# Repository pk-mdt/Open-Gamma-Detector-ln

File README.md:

# Open Gamma Detector

**This is a revised hardware design from the original 3.0 version of the project. The project has been redesigned in Kicad and incorporates an impedance controlled 4 layer board design, as well as micro SMA connectors to the SiPM**

These changed from the original project are hardware only, the original software works and has been fully tested on these revisions. Here is an assembled prototype with a Sodium Iodide Crystal from OST Photonics.

Revised custom layout and hardware for a hackable scintillation counter and multichannel analyzer (MCA) all-in-one device using a popular NaI(Tl) scintillation crystal and a silicon photomultiplier (SiPM). Extremely affordable design for a DIY gamma spectroscopy setup with a total parts cost of under around 200 USD.

The detector uses a standard serial-over-USB connection so that it can be integrated into as many other projects as possible, for example data logging with a Raspberry Pi, weather stations, Arduino projects, etc.

If you want a barebone version of the Open Gamma Detector to count pulses or something like that, you can have a look at the [Mini SiPM Driver](https://github.com/OpenGammaProject/Mini-SiD) board.

## Features

Here are some of the most important specs:

* Compact design: Total size 77 x 50 mm.
* All-in-one: No external parts (e.g. sound card) required to record gamma spectra.
* Easily programmable using drag-and-drop firmware files or the standard Arduino IDE.
* Low-voltage device: No HV needed like with photomultiplier tubes.
* Can use SiPMs in the voltage range of 27.5 V to 33.8 V.
* 4096 ADC channels with built-in 3 V voltage reference.
* Revised Energy resolution of ~6% @ 662 keV possible; highly dependent on your SiPM/scintillator assembly.
* Default (Energy) Mode: About 15 µs total dead time while measuring energy.
* Geiger Mode: About 5 µs total dead time without energy measurements.
* Low power consumption: ~25 mA @ 5 V with default firmware.
* Additional broken-out power pins and I2C, SPI and UART headers for custom parts (e.g. display, µSD card, etc.).
* Built-in True Random Number Generator.
* Simple OLED support out of the box (SSD1306 and SH110x).
* Built-in customizable ticker support.

## Working Principle

Here is a nice flow chart to describe how the device roughly works:

## Hardware

Hardware design has been done with Kicad and all the needed files for you to import the project as well as the schematic can be found in the `hardware` folder. There is also a Gerber file available for you to go directly to the PCB manufacturing step.

Detailed information about the hardware of the detector as well as the potentiometer settings and assembly can be found in the [hardware directory](/hardware/).

## Software

The software aims to be as simple as possible to understand and maintain. To achieve this I decided to use an off-the-shelf microcontroller - the [Raspberry Pi Pico](https://www.raspberrypi.com/products/raspberry-pi-pico/). This board can be programmed with the Arduino IDE over micro-USB and is powerful (dual core, fast ADC, plenty of memory, ...) enough for the purpose and also exceptionally cheap.

To program the Pico and/or play around with the firmware, head to the [software directory](/software/). There you will also find documentation on the serial interface (!), display support, and much more.

## Example Spectra

Coming Soon

## Known Limitations

1. The Raspberry Pi Pico's ADC has some pretty [severe DNL issues](https://pico-adc.markomo.me/INL-DNL/#dnl) that result in four channels being much more sensitive (wider input range) than the rest. For now the simplest solution was to discard all four of them, by printing a `0` when any of them comes up in the measurement (to not affect the cps readings). You can turn this behavior off by using the `set correction` command. This is by no means perfect or ideal, but it works for now until this gets fixed in a later hardware revision of the RP2040 (wish us luck!).

2. Due to the global parts shortage many chips are much harder to come by, if at all that is. Parts that are listed in the BOM should be available easily and with high reliability and stock so that they don't run out quickly. Please let me know if you cannot find a part anymore.

3. The power supply is currently **not** temperature corrected, meaning changes in the ambient temperature with a constant voltage affect the gain of the SiPM. This will naturally result in a different DC bias, energy range and S/N ratio. This effect is negligible around room temperature, though. The temperature dependence of the gain is -0.8%/°C (21°C) for the MicroFC SiPMs.

## Troubleshooting and FAQ

Please have a look at [REFERENCE.md](REFERENCE.md) for some general guidance.

If this doesn't help you, feel free to reach out and create an issue or open a discussions thread.

## Some Ideas

### Coincidence Measurements

Using multiple detector boards with some firmware modifications it should be theoretically possible to implement a coincidence measurement feature. By respectively connecting the `VSYS`, `GND` and one of the broken-out pins to each other on both boards you have everything you need to get started. The pins would be used for an interrupt from the child detector to the parent to trigger a pulse if both timings coincide.

At the moment, though, I couldn't get a coincidence mode feature running due to some weird timing issues. There might be a firmware update in the future to implement this feature. If you have any ideas, let me know!

### Cooling the SiPM

During operation all the electronics including the SiPM naturally heat up ever so slightly. Due to the detector board (where most of the power is dissipated) not being directly connected to the SiPM self-heating is negligible, though. Therefore air or water cooling alone won't improve performance considerably, because it won't heat up much above ambient temps, if at all that is. However, you could cool the SiPM PCB with a Peltier module to sub-ambient temperatures. According to the [datasheet AND9770 (Figure 27)](https://www.onsemi.com/pub/Collateral/AND9770-D.PDF) every 10°C reduction in temperature decreases the dark count rate by 50%! But be sure to correct the SiPM voltage (overvoltage) in this case as it also changes with temperature.

Note that the required breakdown voltage of the SiPM increases linearly with 21.5 mV/°C, see the [C-Series SiPM Sensors Datasheet](https://www.onsemi.com/pdf/datasheet/microc-series-d.pdf). This means that you would also need to temperature correct the PSU voltage if you wanted to use it with considerably different temperatures.

### Shielding Background Radiation

Shielding the ambient background can be done ideally using a wide enough layer of lead (bricks) all around the detector with a thin layer of lower-Z material on the inside such as copper to avoid backscattering. The SiPM and the sample can then be put into the structure to get the best measurements possible (low background).

See Wikipedia: [Lead Castle](https://en.wikipedia.org/w/index.php?title=Lead_castle&oldid=991799816)

---

Thanks for reading.

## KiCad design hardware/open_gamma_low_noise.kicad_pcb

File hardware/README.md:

# Hardware

_Here you can find everything you need to build yourself a detector, or more._

This project utilizes a silicon photomultiplier (short SiPM) which is way smaller and more robust than a traditional photomultiplier tube and does not need a high-voltage supply (traditionally ~1000 V).

The following 6 mm SiPMs are recommended for this project:

* **MICROFC-60035-SMT-TR**
* MICROFC-60035-SMT-TR1 (the exact same as above, however will be more expensive to purchase as sold in smaller batches to suppliers)
* AFBR-S4N66C013 (a good replacement if the above are unavailable)

Here are some very helpful in-depth datasheets about the particular MicroFC SiPM recommended here:

* [C-Series SiPM Sensors datasheet](https://www.onsemi.com/pdf/datasheet/microc-series-d.pdf)
* [Linearity of the Silicon Photomultiplier](https://www.onsemi.com/pub/Collateral/AND9776-D.PDF)
* [Introduction to the SiliconPhotomultiplier (SiPM)](https://www.onsemi.com/pub/Collateral/AND9770-D.PDF)
* [Biasing and Readout of ON Semiconductor SiPM Sensors](https://www.onsemi.com/pub/Collateral/AND9782-D.PDF)

The hardware consists of the main detector (hardware in this folder) which includes amplification, pulse detection and energy measurement. If you already have a SiPM/crystal assembly compatible with voltages around 30 V, you may use it with the detector board and connecting wires directly to the correct pads. Otherwise, you can use my [SiPM carrier board](https://github.com/OpenGammaProject/MicroFC-SiPM-Carrier-Board), which holds the SiPM and all the optional decoupling. There is also a carrier board for the Broadcom SiPM.

The heart of the detector board is the Raspberry Pi Pico which uses its ADC to measure the pulse amplitude (i.e. the energy) immediately after an event occurs starting with an interrupt. I can really recommend you reading the datasheet or maybe also having a look at a deeper analysis of the Pico ADC, if you're interested:

* [Raspberry Pi Pico](https://datasheets.raspberrypi.com/pico/pico-datasheet.pdf)
* [Characterizing the Raspberry Pi Pico ADC](https://pico-adc.markomo.me/)

Here is sa front render of the detector PCB. Size is about 77 x 50 mm. 

On the front side of the PCB at JP1 there is also a jumper to connect the analog ground to the rest of the ground plane. You can solder that if you want to, if you know exactly what you're doing. It's not needed, though.

There are also broken-out pins for the power supply, I2C, SPI and UART connections. These can be used to modify the device, e.g. by adding a display or using a battery charger. You can have a look at the great [Raspberry Pi Pico datasheet](https://datasheets.raspberrypi.com/pico/pico-datasheet.pdf) for more info on this.

Some more info on the peripheral headers can be found in the `software` section of this project.

## Pinout

You can also put a little jumper from `VBUS` to `VSYS` if you **only** want to use the detector with the USB connection on the Pico. This bridges a diode on the Raspberry Pi Pico and saves you a couple of mW.

## Potentiometers

Here is a helpful image about the potentiometer settings for revision 3.0, it's not complicated:

As you can see it is pretty easy to set the required voltage and threshold. **As a general rule, turn any potentiometer clockwise to increase the parameters, turn anti-clockwise to decrease.**

## Scintillator (Assembly)

The finished [MicroFC-](https://github.com/OpenGammaProject/MicroFC-SiPM-Carrier-Board) and [AFBR-](https://github.com/OpenGammaProject/AFBR-SiPM-Carrier-Board) SiPM carrier boards are there to allow for easier packaging with the scintillator as well as to be reusable for different detectors as that's by far the single most expensive part and you'll want to use it as long as possible.

If you are using a larger-diameter scintillator, it might be better for you to use something like the [MicroFC SiPM Array Board](https://github.com/OpenGammaProject/MicroFC-SiPM-Array-Board), which has a 2x2 matrix of SiPMs resulting in 4x the active area. This can increase the energy resolution for large crystals.

### Scintillator Cyrstals

I got all of my scintillators (used NaI(Tl), LYSO, ...) on eBay. Just search for some keywords or specific types, you'll probably find something. Just be sure to look out for signs of wear and tear like scratches on the window or yellowing (!) in NaI crystals as these can deteriorate performance significantly.

You can obviously also buy brand-new scintillators, however, these can be much more expensive. It really depends on the manufacturer there. You can get some cheap 1" x 1" NaI(Tl) scintillator from China for < $100.

Two sources of new NaI(Tl) scintillators are:

| Brand | Location | Comment |
|-------|----------|---------|
|[OST - Photonics](https://www.ost-photonics.com/products/scintillation-crystal/encapsulated-scintillator/standard-type-naitl-scintillator/)| China | Can purchase directly from website |
| [Epic-Crystal](https://www.epic-crystal.com/) | China | Also sold by [GammaSpectacular](https://www.gammaspectacular.com/)

**Since this is a fixed-gain device, I can only highly recommend you to get a scintillator that fits on the PCB and is of a comparable volume as the scintillators I tested. I am using an 18 x 30 mm crystal for most of the spectra that you can see here and it works great. Also, due to the small size of the SiPM in comparison to the scintillator opening, try to use narrower crystals than wider ones if you can.** That way, there aren't many light losses to the SiPM. In general, just be sure the volume/size is not orders of magnitue larger or smaller. If that's not possible, consider using the array board.

If the scintillator is too small, the output voltage too will be very low and you might get restricted by the ADC resolution. In this case the energy range will also be much higher than you would ever need (can easily get up to 10 MeV).

If the scintillator is too large, the output voltages will be very high and thus decrease your energy range dramatically. The device is limited by the 3.0 V reference voltage in this case!

**As a general rule of thumb, try to use as much of the space available on the PCB as possible to mount the scintillator and you will (in most cases) be absolutely fine.**

### Index-Matching Material

You should apply some optical coupling compound between the SiPM and the crystal window to reduce reflections as good as possible (this way the best photon detection efficiency is achieved). There a multitude of options for optical couplants, and depending on your region some may be easier to aquire than others. As a general rule of thumb, silicone oil/grease can be used. If it contains polydimethylsiloxane, you're on the right track. Some options:

<!---This is a good source https://www.logwell.com/tech/servtips/optical_coupling_grease.html - Sebyon --->

| Description            | Brand  | Reflective Index | Viscosity (cPs)| Cost (USD) | Comment |
|------------------------|--------|------------------|----------------|------------|---------|
|[Index Matching Gel, 3 cc](https://www.thorlabs.com/thorproduct.cfm?partnumber=G608N3)|Thorlabs| 1.43 | 1,060,000 | $47.46 | High viscosity, works well for fibre optic coupling. |
|[Index-Matching Fluid](https://www.newport.com/f/index-matching-fluid) | Newport | 1.52 | 100 | $45.60 | Low viscosity may make setting the SiPM and crystal window difficult. However, the RI is the closer to the window properties. Use if you're experienced with assembly. |
|XIAMETER™ PMX-200 Silicone Fluid | Dow Corning | 1.40 | 60,000 - 100,000 | Depends on source | Low cost and [used in research](https://pubs.acs.org/doi/10.1021/acs.cgd.0c00256) due to performance / price. PMX-200 can come in various viscosities, try to get close to 100,000 cPs. |
|Molykote Industrial 4 Electrical Insulating Compound | Dow Corning | N/A | Grease | ~$20 | Used by Ludlum for their survey meter scintillation detectors. |

<!--- I might add some more options for achieving a hermatic seal with tape here once I start putting one together - Sebyon --->

After you applied some, you press both parts together and wrap everything with light-tight tape, again, I'm just using some black electrical tape here. That's essentially it, now you can solder some wires to the pads on the board to connect them together and secure it in place in the free space on the board.

It's very important to get the SiPM/scintillator assembly light-tight. Otherwise you'll either run into problems with lower energies where noise dominates or outright not measure anything at all, because the sensor is saturating.

**==> More assembly instructions can be found on the [Hackaday.io project page](https://hackaday.io/project/185211/instructions)!**

## Raspberry Pi Pico W

Since the Pico W has functionally the exact same size and pinout, it can be a trivial replacement for the standard Pico. This can be a great place to start experimenting with connecting to the Open Gamma Detector via Bluetooth or WiFi, there are endless possibilities what you can do with that.

If you switch to the Pico W, though, you will need to modify the stock firmware slightly since internal pins like the input voltage pin are changed.

There is also no firmware build for the Pico W and I don't plan to make one in the near future, since I'm busy enough with the stock firmware, hardware and Gamma MCA, to start building yet another Bluetooth- or WiFi-connected app or whatever.

I'll happily accept PRs if you make something like that, though, so let me know! ;)

## Shielding

Due to the detector measuring small voltages, energy resolution being limited by noise and a small 470 pF capacitor being on board, it is generally pretty sensitive to EMI. For the best performance possible, you should put your detector into some kind of metal enclosure. It doesn't need to be a thick metal case, a tin can will most likely suffice.

<!--- Once I start assembly I'll look at proving some shielding ideas - Sebyon --->

The four screw holes on the PCB's actual detector part are connected to the circuit GND.

As some level of protection against EMI, the peak and hold capacitor is periodically discharged as to avoid it being charged ever so slightly by interference. This takes place every millisecond by default and cannot be switched on or off via a serial command. This adds less than 1% of additional dead time (~2.5 µs per reset), so should be completely negligible.

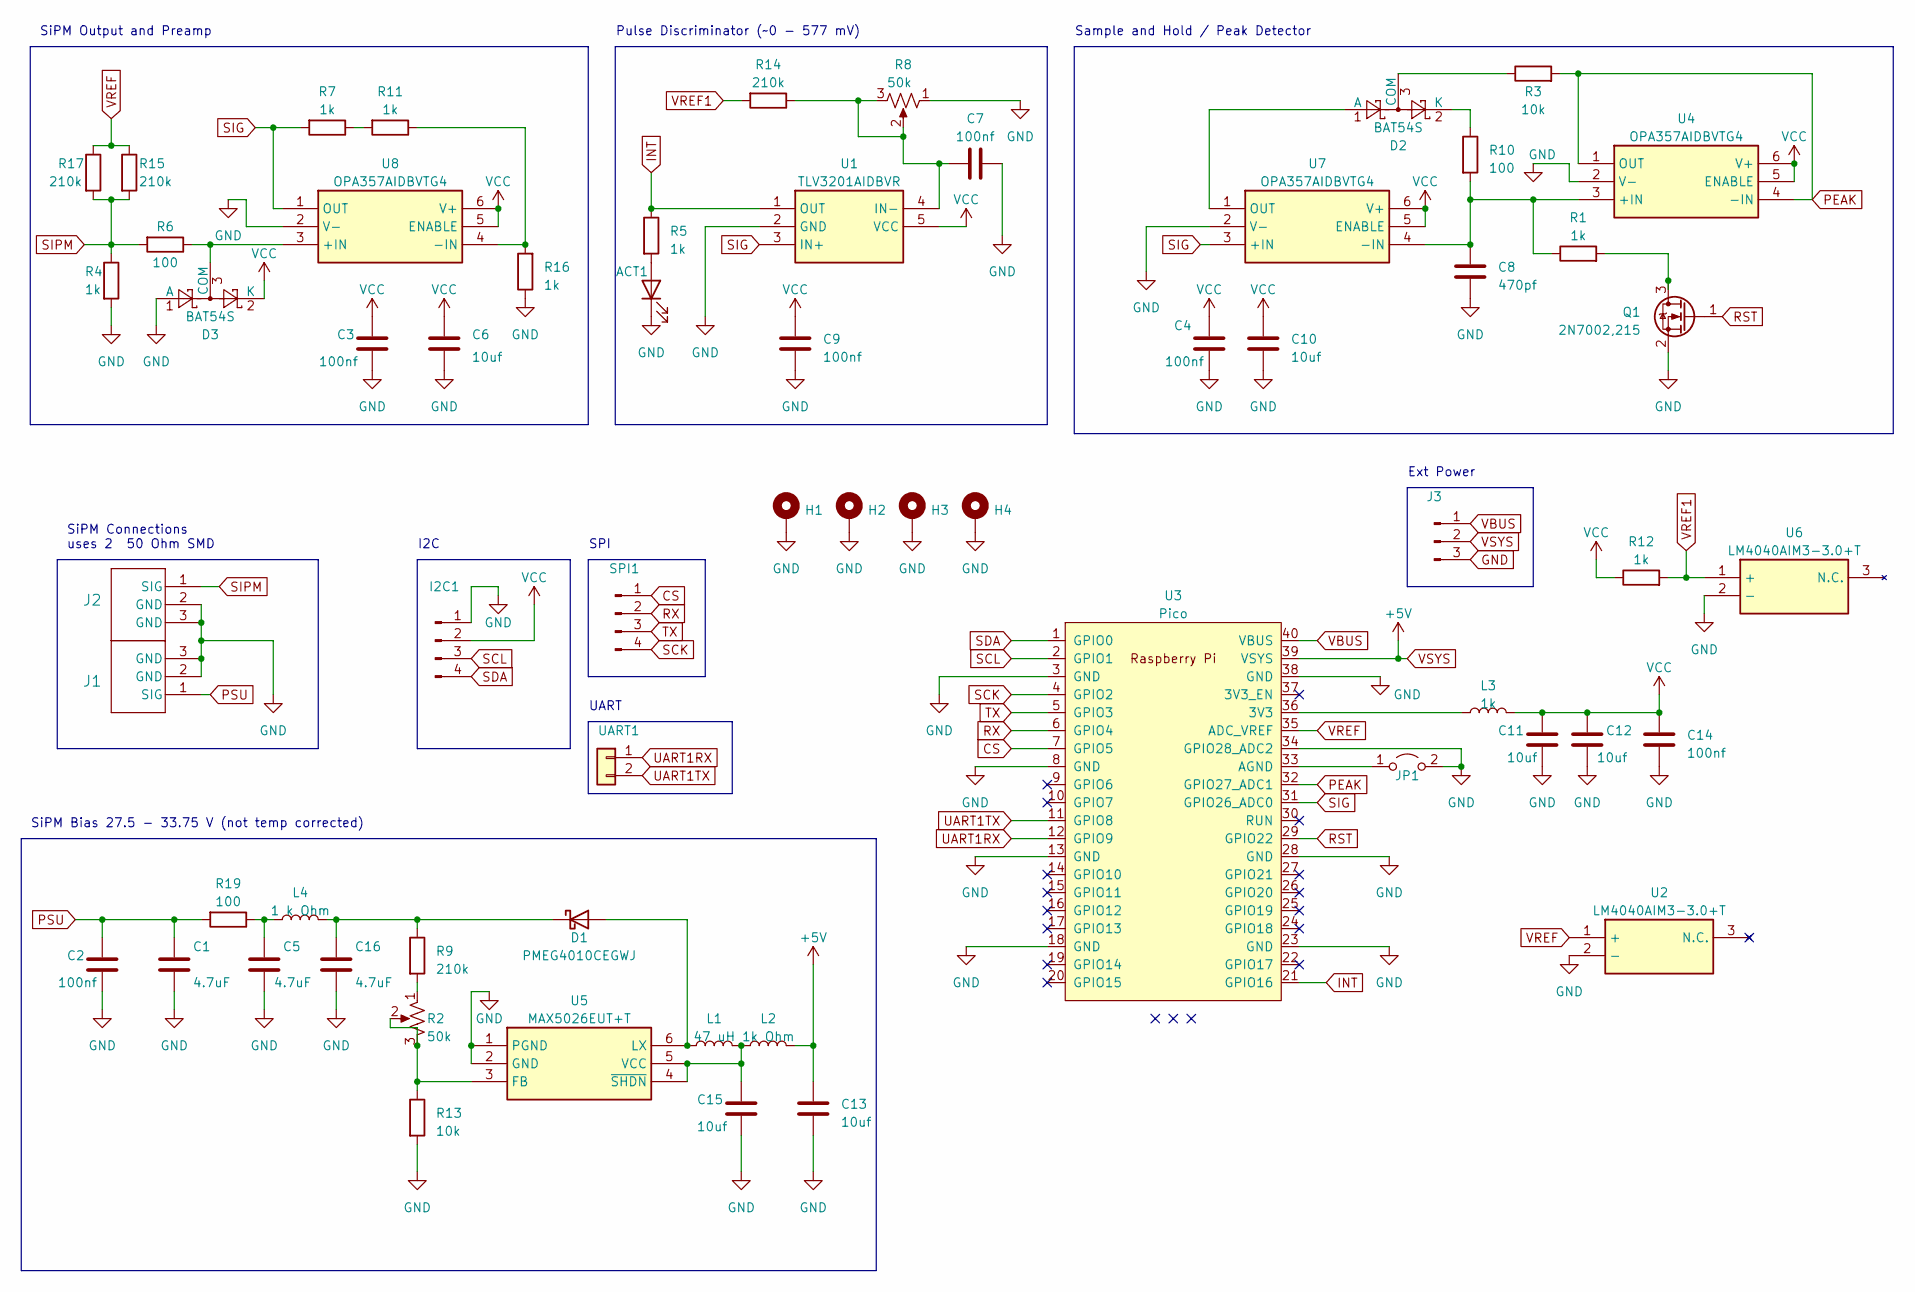
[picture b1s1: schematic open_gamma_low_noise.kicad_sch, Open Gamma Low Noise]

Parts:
ACT1: LED; LED_0805_2012Metric
C1, C5, C16: 4.7uF; C_0805_2012Metric
C2, C3, C4, C7, C9, C14: 100nf; C_0603_1608Metric
C6, C10, C11, C12, C13, C15: 10uf; C_0603_1608Metric
C8: 470pf; C_0603_1608Metric
D1: PMEG4010CEGWJ; SODFL3516X120N
D2, D3: BAT54S; SOT-23
H1, H2, H3, H4: MountingHole_2.2mm_M2_Pad_Via
I2C1: PinHeader_1x04_P2.54mm_Vertical
J1, J2: 1909763-1; CONN3_1909763_TEC
J3: PinHeader_1x03_P2.54mm_Vertical
JP1: Jumper_2_Open; SolderJumper-2_P1.3mm_Open_RoundedPad1.0x1.5mm
L1: 47 uH; 74404054470
L2: 1k Ohm; L_0603_1608Metric
L3: 1k; L_0603_1608Metric
L4: 1 k Ohm; L_0603_1608Metric
Q1: 2N7002,215; SOT-23
R1, R4, R5, R7, R11, R12, R16: 1k; R_0603_1608Metric
R2, R8: 50k; POT_3296W
R3, R13: 10k; R_0603_1608Metric
R6, R10, R19: 100; R_0603_1608Metric
R9, R14, R15, R17: 210k; R_0603_1608Metric
SPI1: Conn_01x04_Pin; PinHeader_1x04_P2.54mm_Vertical
U1: TLV3201AIDBVR; SOT95P280X145-5N; Mouser Part Number 595-TLV3201AIDBVR
U2, U6: LM4040AIM3-3.0+T; SOT95P237X112-3N; Mouser Part Number 700-LM4040AIM3-3.0T
U3: Pico; RPi_Pico_SMD_TH
U4, U7, U8: OPA357AIDBVTG4; SOT95P280X145-6N; Mouser Part Number 595-OPA357AIDBVTG4
U5: MAX5026EUT+T; SOT95P280X145-6N; Mouser Part Number 700-MAX5026EUTT
UART1: Conn_01x02; PinHeader_1x02_P2.54mm_Vertical

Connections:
CS: SPI1.1, U3.7 (GPIO5); also elsewhere on the board
GND: ACT1.1 (K), C1.2, C2.2, C3.2, C4.2, C5.2, C6.2, C7.2, C8.2, C9.2, C10.2, C11.2, C12.2, C13.2, C14.2, C15.2, C16.2, D3.1 (A), H1.1, H2.1, H3.1, H4.1, I2C1.1, J1.2 (GND), J1.3 (GND), J2.2 (GND), J2.3 (GND), J3.3, JP1.2 (B), Q1.2 (S), R4.2, R8.1, R13.2, R16.1, U1.2 (GND), U2.2 (-), U3.3 (GND), U3.8 (GND), U3.13 (GND), U3.18 (GND), U3.23 (GND), U3.28 (GND), U3.34 (GPIO28_ADC2), U3.38 (GND), U4.2 (V-), U5.1 (PGND), U5.2 (GND), U6.2 (-), U7.2 (V-), U8.2 (V-); also elsewhere on the board
INT: R5.1, U1.1 (OUT), U3.21 (GPIO16)
unnamed: ACT1.2 (A), R5.2
unnamed: C5.1, L4.1, R19.1
unnamed: D1.2 (A), L1.1, U5.6 (LX)
unnamed: C16.1, D1.1 (K), L4.2, R9.1
unnamed: D2.1 (A), U7.1 (OUT)
unnamed: D2.3 (COM), R3.1
unnamed: D2.2 (K), R10.1
unnamed: D3.3 (COM), R6.1, U8.3 (+IN)
unnamed: JP1.1 (A), U3.33 (AGND)
unnamed: Q1.3 (D), R1.2
unnamed: R2.1, R9.2
unnamed: R7.1, R11.2
unnamed: C7.1, R8.2, R8.3, R14.1, U1.4 (IN-)
unnamed: L3.1, U3.36 (3V3)
unnamed: C8.1, R1.1, R10.2, U4.3 (+IN), U7.4 (-IN)
unnamed: R2.2, R2.3, R13.1, U5.3 (FB)
unnamed: C15.1, L1.2, L2.1, U5.4 (~SHDN), U5.5 (VCC)
unnamed: R11.1, R16.2, U8.4 (-IN)
PEAK: R3.2, U3.32 (GPIO27_ADC1), U4.1 (OUT), U4.4 (-IN)
PSU: C1.1, C2.1, J1.1 (SIG), R19.2
RST: Q1.1 (G), U3.29 (GPIO22)
RX: SPI1.2, U3.6 (GPIO4); also elsewhere on the board
SCK: SPI1.4, U3.4 (GPIO2); also elsewhere on the board
SCL: I2C1.3, U3.2 (GPIO1); also elsewhere on the board
SDA: I2C1.4, U3.1 (GPIO0); also elsewhere on the board
SIG: R7.2, U1.3 (IN+), U3.31 (GPIO26_ADC0), U7.3 (+IN), U8.1 (OUT)
SIPM: J2.1 (SIG), R4.1, R6.2, R15.2, R17.2
TX: SPI1.3, U3.5 (GPIO3); also elsewhere on the board
UART1RX: U3.12 (GPIO9), UART1.1; also elsewhere on the board
UART1TX: U3.11 (GPIO8), UART1.2; also elsewhere on the board
VBUS: J3.1, U3.40 (VBUS)
VCC: C3.1, C4.1, C6.1, C9.1, C10.1, C11.1, C12.1, C14.1, D3.2 (K), I2C1.2, L3.2, R12.1, U1.5 (VCC), U4.5 (ENABLE), U4.6 (V+), U7.5 (ENABLE), U7.6 (V+), U8.5 (ENABLE), U8.6 (V+); also elsewhere on the board
VREF: R15.1, R17.1, U2.1 (+), U3.35 (ADC_VREF)
VREF1: R12.2, R14.2, U6.1 (+)
VSYS: C13.1, J3.2, L2.2, U3.39 (VSYS)

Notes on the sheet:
SPI
Ext Power
Pulse Discriminator (~0 - 577 mV)
SiPM Output and Preamp
I2C
Sample and Hold / Peak Detector
SiPM Bias 27.5 - 33.75 V (not temp corrected)
UART
SiPM Connections uses 2 50 Ohm SMD

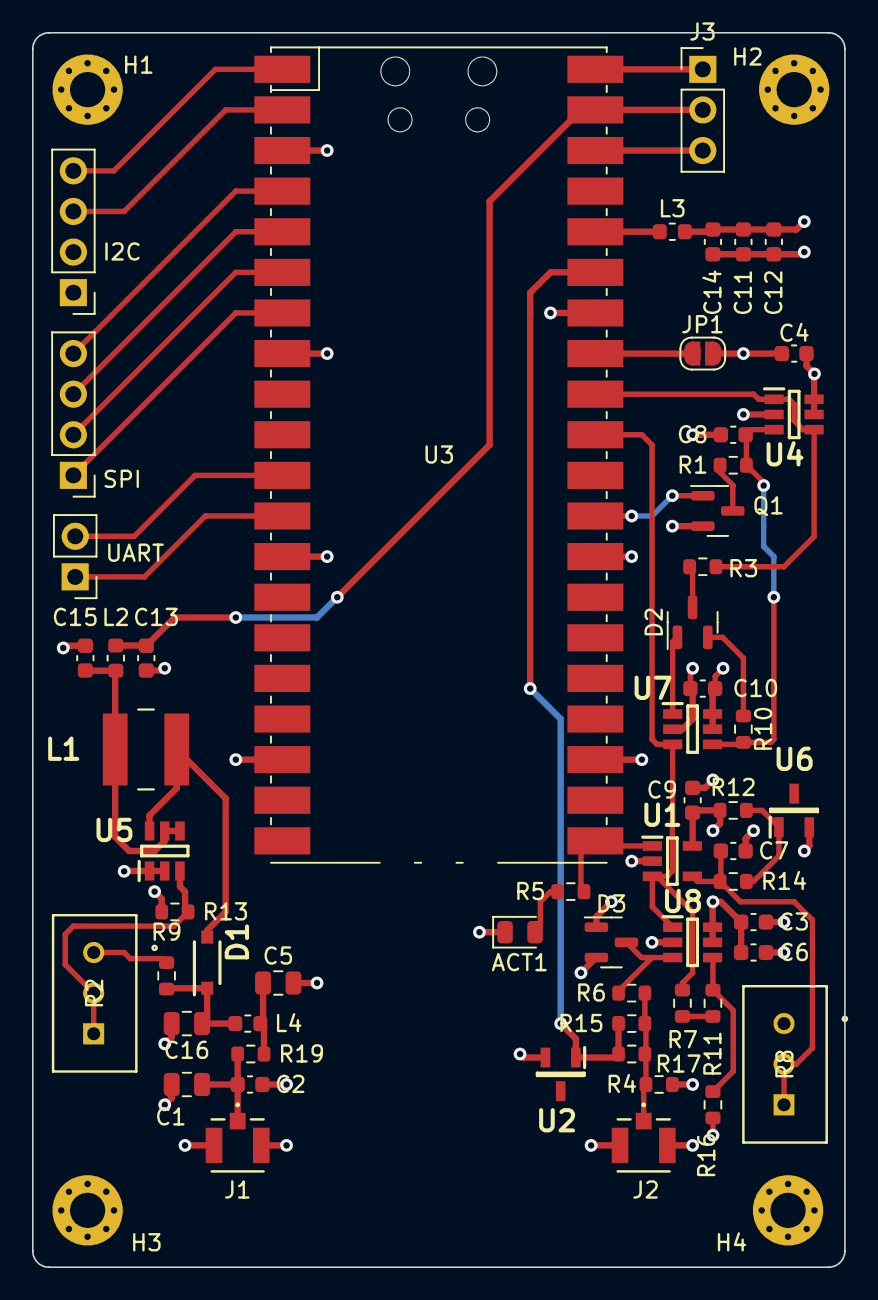
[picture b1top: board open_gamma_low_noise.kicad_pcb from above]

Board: 4 copper layers, 50.8 x 77.2 mm, 62 parts (0 on the bottom side), 38 nets.

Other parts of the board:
I2C: PinHeader_1x04_P2.54mm_Vertical
SPI: Conn_01x04_Pin; PinHeader_1x04_P2.54mm_Vertical
UART: Conn_01x02; PinHeader_1x02_P2.54mm_Vertical

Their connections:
CS: SPI.1; also elsewhere on the board
GND: I2C.1; also elsewhere on the board
RX: SPI.2; also elsewhere on the board
SCK: SPI.4; also elsewhere on the board
SCL: I2C.3; also elsewhere on the board
SDA: I2C.4; also elsewhere on the board
TX: SPI.3; also elsewhere on the board
UART1RX: UART.1; also elsewhere on the board
UART1TX: UART.2; also elsewhere on the board
VCC: I2C.2; also elsewhere on the board

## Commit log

2023-07-26 Low Noise Hardware Revisions
    Changed to 4 layer impedance controlled board. Redesigned using kicad.
2023-07-26 Update README.md
    Removed STL Files for new design until the 3D design completed
2023-07-26 Removed Enclosure
    Removed 3D files until rework completed
2023-07-26 Update README.md
    Remove Case References (for now)
2023-07-26 Revised Images
2023-07-26 Update README.md
    Revised Images
2023-07-26 Updated 3D models
